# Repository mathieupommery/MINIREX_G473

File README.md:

# STM32G473 Flight Controller (20x20mm)

# NEWS : 
* V2 reduced cost by changing part of the compoment to asian brand, assembly now possible with jlc and lcsc part stock, a price per unit produced graph is disponible below 

## Overview
High-performance flight controller based on the **STM32G473** MCU, featuring a compact 20x20mm mounting pattern. This board is specifically designed for high-voltage builds (up to 12S) and high-speed processing, utilizing a 6-layer PCB stackup with all components mounted on a single side for optimal integration and cooling.
## Hardware Visuals

### PCB View (V1)

### CAD View (V1)

## Technical Specifications
### Core System
* **MCU:** STM32G473 (Cortex-M4, 170MHz)
* **IMU:** ICM-42688-P (Ultra-low noise 6-axis gyro)
* **Blackbox:** 16M-bit (2MB) Onboard Flash
* **PCB:** 6-layer, single-sided compoment 

### Power Management
* **Main Buck Regulator:** LMR51625
    * **Input Voltage:** 7V to 55V
    * **Output:** 5V @ 2.5A Max
* **Dual LDO Regulation:** Two independent LDL212PV33R (1.2A each)
    * **LDO 1:** Dedicated to MCU and Flash memory
    * **LDO 2:** Dedicated to the ICM-42688-P sensor for maximum signal purity

### Protection & Hardware Robustness
* **USB Protection:** Integrated **TVS Diodes** (Transient Voltage Suppressors) on the USB port to protect the MCU against electrostatic discharge (ESD) and short-circuits caused by humidity or debris.
* **Filtering:** High-quality ceramic capacitors and dedicated power planes for a low noise floor.

### Connectivity & Interface
* **Connectors:** 2x JST-SH 1.0mm ports (DJI/Digital VTX and ESC)
* **Status LEDs:** 4x Onboard diagnostic LEDs:
    * 2x Betaflight Status (Green/Blue)
    * 1x 3.3V MCU Power
    * 1x 3.3V Sensor Power
    * many soldering pads to add GPS, buzzer, led, or IO 

## Cost (BOM)
## Bill of Materials (BOM) Cost Estimation

The following table demonstrates the estimated component costs based on Mouser volume pricing. The unit price of each component dynamically adapts to the total quantity required for the entire production batch (1, 100, or 1000 boards). 

*Prices are estimates in USD and do not include PCB manufacturing or assembly costs.*

| Component / Value | Mouser Ref. | Qty/Board | Unit Price (1 Bd) | Unit Price (100 Bds) | Unit Price (1k Bds) | Total 1 Bd | Total 100 Bds | Total 1k Bds |
| :--- | :--- | :---: | :---: | :---: | :---: | :---: | :---: | :---: |
| 100n | 710-885012104005 | 13 | $0.080 | $0.010 | $0.004 | $1.04 | $13.00 | $52.00 |
| 10n | 710-885012104014 | 1 | $0.120 | $0.030 | $0.010 | $0.12 | $3.00 | $10.00 |
| 1u | 710-885012105012 | 3 | $0.180 | $0.060 | $0.030 | $0.54 | $18.00 | $90.00 |
| 4.7u | 710-885012105012 | 3 | $0.180 | $0.060 | $0.030 | $0.54 | $18.00 | $90.00 |
| 0.1u | 81-GRM155R62A104ME4J | 1 | $0.100 | $0.020 | $0.010 | $0.10 | $2.00 | $10.00 |
| 2.2u | 710-885012105007 | 1 | $0.220 | $0.080 | $0.040 | $0.22 | $8.00 | $40.00 |
| 2.2u | 81-GRT21BD72A225KE13 | 2 | $0.240 | $0.090 | $0.050 | $0.48 | $18.00 | $100.00 |
| 47u | 81-GRM21BR61A476ME5K | 2 | $0.550 | $0.220 | $0.120 | $1.10 | $44.00 | $240.00 |
| USB4110-GF-A | 710-629722000214 | 1 | $1.150 | $0.850 | $0.650 | $1.15 | $85.00 | $650.00 |
| LED 150040BS73240 (Blue) | 710-150040BS73240 | 1 | $0.260 | $0.120 | $0.080 | $0.26 | $12.00 | $80.00 |
| LED 150040GS73240 (Green) | 710-150040GS73240 | 1 | $0.260 | $0.120 | $0.080 | $0.26 | $12.00 | $80.00 |
| LED 150040RS73240 (Red) | 710-150040RS73240 | 2 | $0.260 | $0.120 | $0.080 | $0.52 | $24.00 | $160.00 |
| STM32G473CEU6 | 511-STM32G473CEU6 | 1 | $7.580 | $5.450 | $4.800 | $7.58 | $545.00 | $4800.00 |
| 5.1k | 667-ERJ-1GNF5101C | 2 | $0.100 | $0.010 | $0.005 | $0.20 | $2.00 | $10.00 |
| 100k | 667-ERJ-1GNF1003C | 2 | $0.100 | $0.010 | $0.005 | $0.20 | $2.00 | $10.00 |
| 10k | 667-ERJ-1GNF1002C | 3 | $0.100 | $0.010 | $0.005 | $0.30 | $3.00 | $15.00 |
| 1k | 667-ERJ-1GNF1001C | 6 | $0.100 | $0.010 | $0.005 | $0.60 | $6.00 | $30.00 |
| 20k | 667-ERJ-1GNF2002C | 1 | $0.100 | $0.010 | $0.005 | $0.10 | $1.00 | $5.00 |
| 19.1k | 667-ERJ-1GNF1912C | 1 | $0.100 | $0.010 | $0.005 | $0.10 | $1.00 | $5.00 |
| 22R | 667-ERJ-1GNF22R0C | 7 | $0.100 | $0.010 | $0.005 | $0.70 | $7.00 | $35.00 |
| 100R | 667-ERJ-1GNF1000C | 1 | $0.100 | $0.010 | $0.005 | $0.10 | $1.00 | $5.00 |
| Ferrite 74279220800 | 710-74279220800 | 1 | $0.140 | $0.040 | $0.020 | $0.14 | $4.00 | $20.00 |
| Inductor 74479335329247 | 710-74479335329247 | 1 | $0.780 | $0.450 | $0.320 | $0.78 | $45.00 | $320.00 |
| JST SH 6-pin | 306-M06BSRSSTBLFSNPP | 1 | $0.640 | $0.420 | $0.310 | $0.64 | $42.00 | $310.00 |
| LDO LDL212PV33R | 511-LDL212PV33R | 2 | $0.530 | $0.380 | $0.280 | $1.06 | $76.00 | $560.00 |
| Flash MX25R1635FZUIH0 | 95-25R1635FZUIH0TR | 1 | $1.840 | $1.150 | $0.950 | $1.84 | $115.00 | $950.00 |
| TVS SP3222-02ETG | 576-SP3222-02ETG | 1 | $0.420 | $0.220 | $0.150 | $0.42 | $22.00 | $150.00 |
| Switch 435151014824 | 710-435151014824 | 1 | $0.850 | $0.520 | $0.380 | $0.85 | $52.00 | $380.00 |
| MOSFET 2N7002KQBZ | 771-2N7002KQBZ | 1 | $0.180 | $0.060 | $0.030 | $0.18 | $6.00 | $30.00 |
| Osc CSTNE8M00GH5C000R0 | 81-CSTNE8M00GH5C000R | 1 | $0.450 | $0.240 | $0.160 | $0.45 | $24.00 | $160.00 |
| IMU ICM-42688-P | 410-ICM-42688-P | 1 | $4.860 | $3.550 | $2.900 | $4.86 | $355.00 | $2900.00 |
| JST SH 8-pin | 306-SM08BSRSSTB | 1 | $0.720 | $0.480 | $0.350 | $0.72 | $48.00 | $350.00 |
| Diode BAT60JFILM | 511-BAT60JFILM | 2 | $0.280 | $0.110 | $0.060 | $0.56 | $22.00 | $120.00 |
| Buck LMR51625YFDDCR | 595-LMR51625YFDDCR | 1 | $1.250 | $0.880 | $0.650 | $1.25 | $88.00 | $650.00 |
| **TOTAL COST (BOM)** | **-** | **-** | **-** | **-** | **-** | **$29.96** | **$1724.00** | **$13417.00** |
| **AVERAGE PRICE PER BOARD** | **-** | **-** | **-** | **-** | **-** | **$29.96** | **$17.24** | **$13.42** |

## Cost (BOM) V2
V2 version is here for cost optimisation purposes and for the possibility to assemble it completly on jlcpcb with lcsc compoment part, i changed few compoment like Nmos for buzzer or boot button, and i priviledged asian brand here is a graph with the cost per unit according to unit produced : 

## Hardware Design Principles
The 6-layer design ensures superior EMI shielding and thermal dissipation. 
stackup: signal-gnd-signal-gnd-power-gnd   
provide shielded power from signal and from the outside.

## Result and test : 

### Before reflow : 

###  Mounted on apex evo 5 inch : 

###  Test in fly :

> La vidéo de démonstration est disponible ici : [DOC/image_v1/video.mp4](./DOC/v1_image/vid.mp4)

## License
Creative Commons Attribution-NonCommercial-ShareAlike 4.0 International.

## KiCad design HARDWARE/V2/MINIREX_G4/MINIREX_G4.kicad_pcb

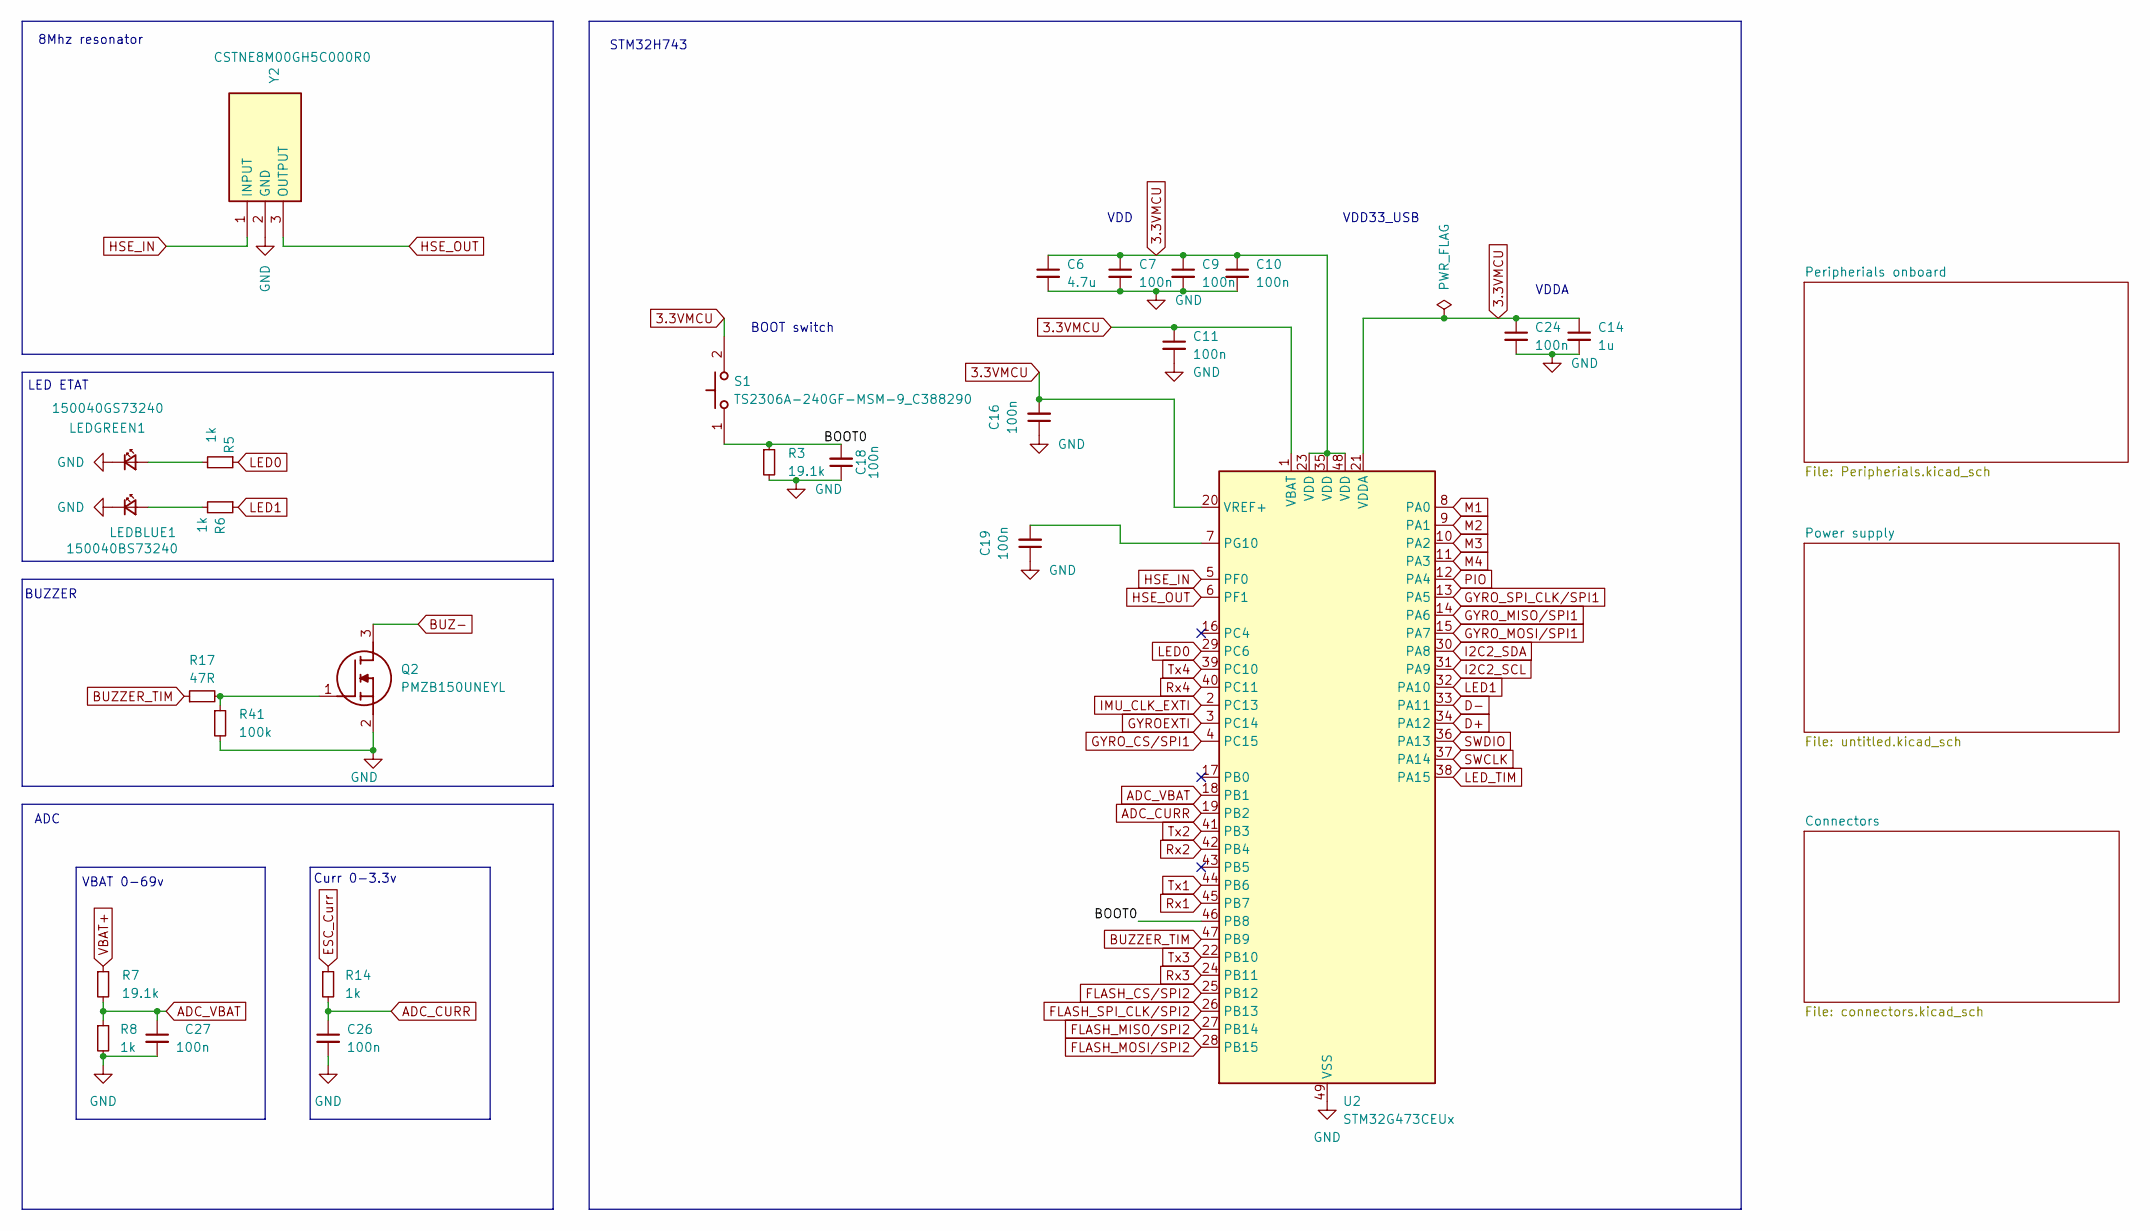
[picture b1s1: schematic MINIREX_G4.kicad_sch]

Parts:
C6: 4.7u; C_0402_1005Metric; Manufacturer_Part_Number CC0402MRX5R7BB475; Mouser Part Number 710-885012105012
C7, C9, C10, C11, C16, C18, C19, C24, C26, C27: 100n; C_0201_0603Metric_Pad0.64x0.40mm_HandSolder; Manufacturer_Part_Number CC0201KRX5R8BB104; Mouser Part Number 710-885012104005
C14: 1u; C_0402_1005Metric; Manufacturer_Part_Number CC0402KRX5R7BB105; Mouser Part Number 710-885012105012
LEDBLUE1: 150040BS73240; LED_0402_1005Metric; Manufacturer_Part_Number XL-1005UBC; Mouser Part Number 710-150040BS73240
LEDGREEN1: 150040GS73240; LED_0402_1005Metric; Manufacturer_Part_Number SZYY0402G; Mouser Part Number 710-150040GS73240
Q2: PMZB150UNEYL; Manufacturer_Part_Number TPM2025NP3; Mouser Part Number 771-PMZB150UNEYL
R3, R7: 19.1k; R_0201_0603Metric_Pad0.64x0.40mm_HandSolder; Manufacturer_Part_Number RC0201FR-0719K6L; Mouser Part Number 667-ERJ-1GNF1002C
R5, R6, R8, R14: 1k; R_0201_0603Metric_Pad0.64x0.40mm_HandSolder; Manufacturer_Part_Number RC0201FR-071KL; Mouser Part Number 667-ERJ-1GNF1001C
R17: 47R; R_0201_0603Metric_Pad0.64x0.40mm_HandSolder; Manufacturer_Part_Number RC0201FR-0747RL; Mouser Part Number 667-ERJ-1GNF22R0C
R41: 100k; R_0201_0603Metric_Pad0.64x0.40mm_HandSolder; Manufacturer_Part_Number RC0201FR-07100KL; Mouser Part Number 667-ERJ-1GNF1003C
S1: TS2306A-240GF-MSM-9_C388290; TS2306A240GFMSM9_C388290; Manufacturer_Part_Number TS2306A-240GF-MSM-9_C388290; LCSC Part Number C2976675
U2: STM32G473CEUx; QFN-48-1EP_7x7mm_P0.5mm_EP5.6x5.6mm; Manufacturer_Part_Number STM32G473CEU6; Mouser Part Number 511-STM32G473CEU6
Y2: CSTNE8M00GH5C000R0; CSTNE12M0GH5L000R0; Mouser Part Number 81-CSTNE8M00GH5C000R

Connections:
3.3VMCU: C6.1, C7.1, C9.1, C10.1, C11.1, C14.1, C16.2, C24.1, S1.2 (COM), U2.1 (VBAT), U2.20 (VREF+), U2.21 (VDDA), U2.23 (VDD), U2.35 (VDD), U2.48 (VDD); also elsewhere on the board
/BOOT0: C18.2, R3.1, S1.1 (NO), U2.46 (PB8)
ADC_CURR: C26.1, R14.2, U2.19 (PB2)
ADC_VBAT: C27.1, R7.2, R8.1, U2.18 (PB1)
BUZ-: Q2.3 (D); also elsewhere on the board
BUZZER_TIM: R17.1, U2.47 (PB9)
D+: U2.34 (PA12); also elsewhere on the board
D-: U2.33 (PA11); also elsewhere on the board
ESC_Curr: R14.1; also elsewhere on the board
FLASH_CS/SPI2: U2.25 (PB12); also elsewhere on the board
FLASH_MISO/SPI2: U2.27 (PB14); also elsewhere on the board
FLASH_MOSI/SPI2: U2.28 (PB15); also elsewhere on the board
FLASH_SPI_CLK/SPI2: U2.26 (PB13); also elsewhere on the board
GND: C6.2, C7.2, C9.2, C10.2, C11.2, C14.2, C16.1, C18.1, C19.1, C24.2, C26.2, C27.2, LEDBLUE1.1 (K), LEDGREEN1.1 (K), Q2.2 (S), R3.2, R8.2, R41.2, U2.49 (VSS), Y2.2 (GND); also elsewhere on the board
GYROEXTI: U2.3 (PC14); also elsewhere on the board
GYRO_CS/SPI1: U2.4 (PC15); also elsewhere on the board
GYRO_MISO/SPI1: U2.14 (PA6); also elsewhere on the board
GYRO_MOSI/SPI1: U2.15 (PA7); also elsewhere on the board
GYRO_SPI_CLK/SPI1: U2.13 (PA5); also elsewhere on the board
HSE_IN: U2.5 (PF0), Y2.1 (INPUT)
HSE_OUT: U2.6 (PF1), Y2.3 (OUTPUT)
I2C2_SCL: U2.31 (PA9); also elsewhere on the board
I2C2_SDA: U2.30 (PA8); also elsewhere on the board
IMU_CLK_EXTI: U2.2 (PC13); also elsewhere on the board
LED0: R5.1, U2.29 (PC6)
LED1: R6.1, U2.32 (PA10)
LED_TIM: U2.38 (PA15); also elsewhere on the board
M1: U2.8 (PA0); also elsewhere on the board
M2: U2.9 (PA1); also elsewhere on the board
M3: U2.10 (PA2); also elsewhere on the board
M4: U2.11 (PA3); also elsewhere on the board
unnamed: LEDBLUE1.2 (A), R6.2
unnamed: LEDGREEN1.2 (A), R5.2
unnamed: Q2.1 (G), R17.2, R41.1
unnamed: C19.2, U2.7 (PG10)
PIO: U2.12 (PA4); also elsewhere on the board
Rx1: U2.45 (PB7); also elsewhere on the board
Rx2: U2.42 (PB4); also elsewhere on the board
Rx3: U2.24 (PB11); also elsewhere on the board
Rx4: U2.40 (PC11); also elsewhere on the board
SWCLK: U2.37 (PA14); also elsewhere on the board
SWDIO: U2.36 (PA13); also elsewhere on the board
Tx1: U2.44 (PB6); also elsewhere on the board
Tx2: U2.41 (PB3); also elsewhere on the board
Tx3: U2.22 (PB10); also elsewhere on the board
Tx4: U2.39 (PC10); also elsewhere on the board
VBAT+: R7.1; also elsewhere on the board

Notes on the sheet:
VDD33_USB
VDDA
BUZZER
STM32H743
ADC
Curr 0-3.3v
LED ETAT
BOOT switch
VDD
8Mhz resonator
VBAT 0-69v

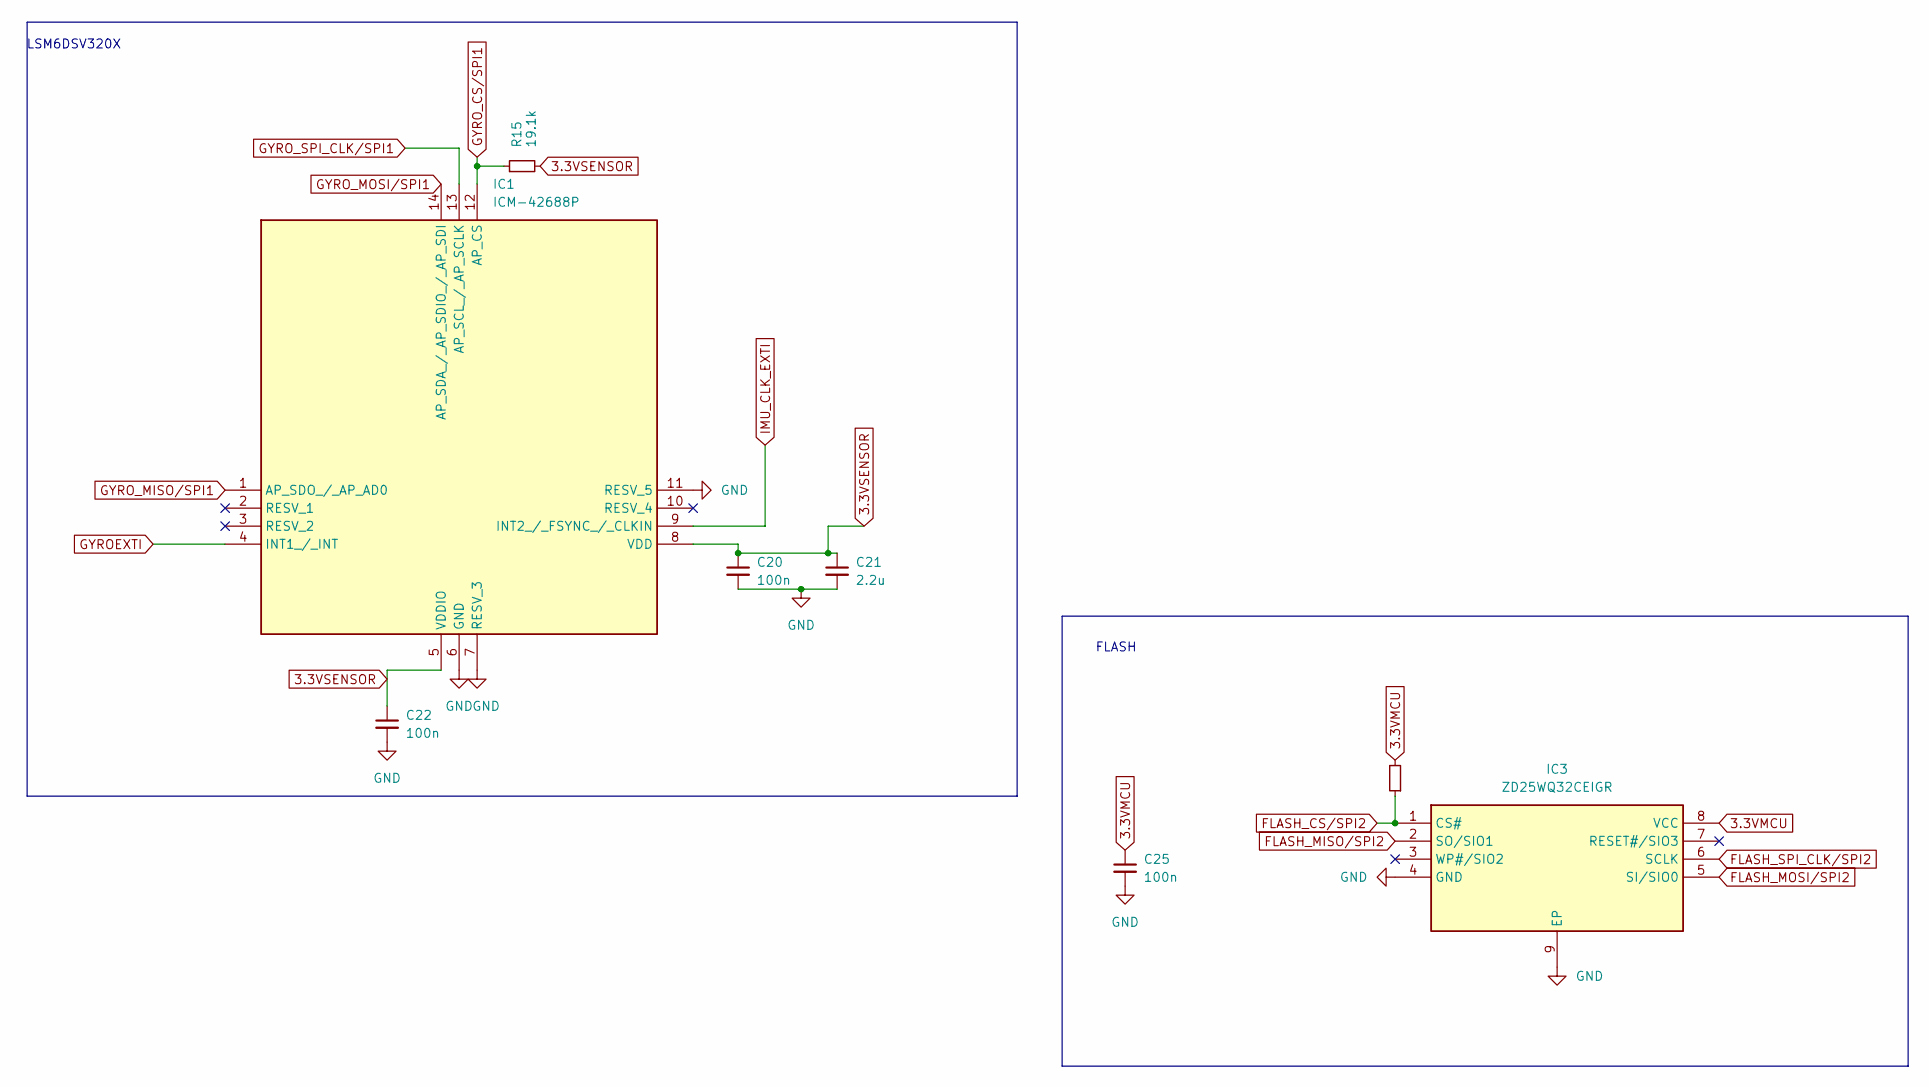
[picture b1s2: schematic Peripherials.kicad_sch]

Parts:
C20, C25: 100n; C_0201_0603Metric_Pad0.64x0.40mm_HandSolder; Manufacturer_Part_Number CC0201KRX5R8BB104; Mouser Part Number 710-885012104005
C21: 2.2u; C_0402_1005Metric; Manufacturer_Part_Number CC0402KRX5R7BB225; Mouser Part Number 710-885012105007
C22: 100n; C_0201_0603Metric_Pad0.64x0.40mm_HandSolder; Manufacturer_Part_Number CC0201KRX5R8BB104; Mouser Part Number 710-885012104014
IC1: ICM-42688P; IIM42352; Mouser Part Number 410-ICM-42688-P
IC3: ZD25WQ32CEIGR; SON50P300X200X60-9N; Manufacturer_Part_Number ZD25WQ32CEIGR; Mouser Part Number 95-25R1635FZUIH0TR
R9, R15: 19.1k; R_0201_0603Metric_Pad0.64x0.40mm_HandSolder; Manufacturer_Part_Number RC0201FR-0719K6L; Mouser Part Number 667-ERJ-1GNF1002C

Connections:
3.3VMCU: C25.1, IC3.8 (VCC), R9.2; also elsewhere on the board
3.3VSENSOR: C20.1, C21.1, C22.1, IC1.5 (VDDIO), IC1.8 (VDD), R15.2; also elsewhere on the board
FLASH_CS/SPI2: IC3.1 (CS#), R9.1; also elsewhere on the board
FLASH_MISO/SPI2: IC3.2 (SO/SIO1); also elsewhere on the board
FLASH_MOSI/SPI2: IC3.5 (SI/SIO0); also elsewhere on the board
FLASH_SPI_CLK/SPI2: IC3.6 (SCLK); also elsewhere on the board
GND: C20.2, C21.2, C22.2, C25.2, IC1.6 (GND), IC1.7 (RESV_3), IC1.11 (RESV_5), IC3.4 (GND), IC3.9 (EP); also elsewhere on the board
GYROEXTI: IC1.4 (INT1_/_INT); also elsewhere on the board
GYRO_CS/SPI1: IC1.12 (AP_CS), R15.1; also elsewhere on the board
GYRO_MISO/SPI1: IC1.1 (AP_SDO_/_AP_AD0); also elsewhere on the board
GYRO_MOSI/SPI1: IC1.14 (AP_SDA_/_AP_SDIO_/_AP_SDI); also elsewhere on the board
GYRO_SPI_CLK/SPI1: IC1.13 (AP_SCL_/_AP_SCLK); also elsewhere on the board
IMU_CLK_EXTI: IC1.9 (INT2_/_FSYNC_/_CLKIN); also elsewhere on the board

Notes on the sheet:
FLASH
LSM6DSV320X

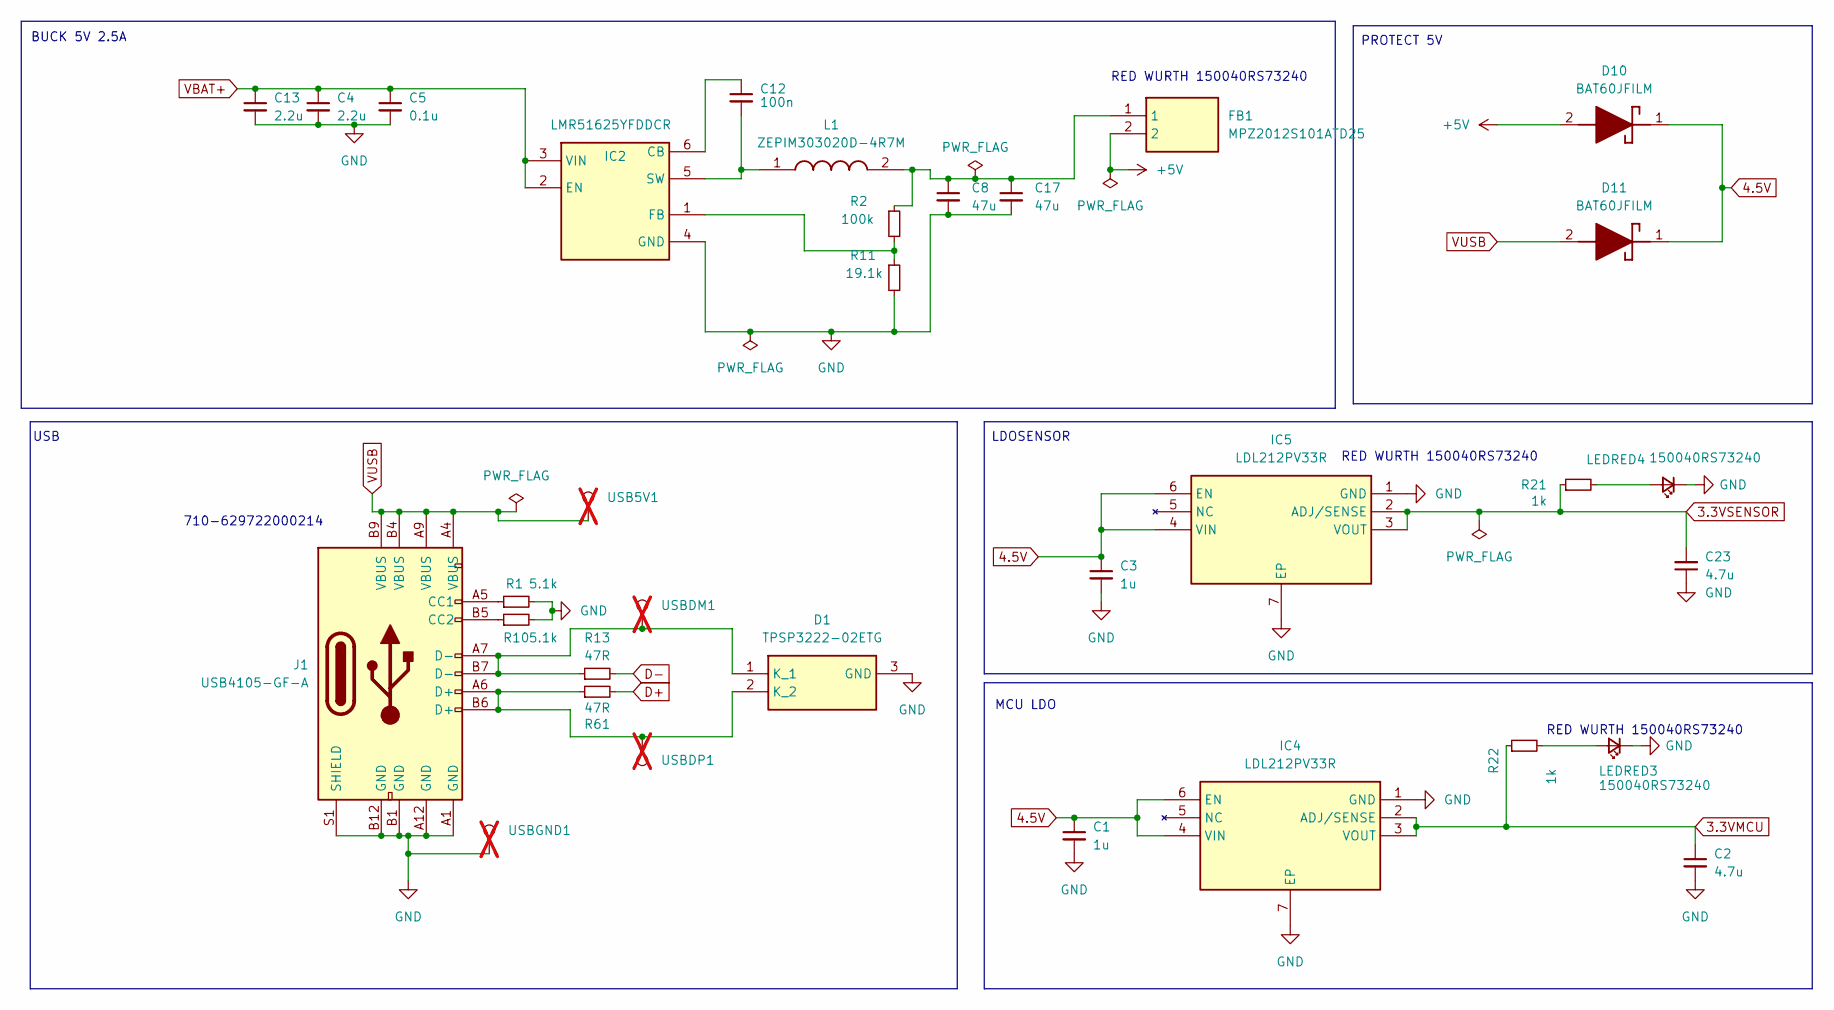
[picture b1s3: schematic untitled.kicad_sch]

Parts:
C1, C3: 1u; C_0402_1005Metric; Manufacturer_Part_Number CC0402KRX5R7BB105; Mouser Part Number 710-885012105012
C2, C23: 4.7u; C_0402_1005Metric; Manufacturer_Part_Number CC0402MRX5R7BB475; Mouser Part Number 710-885012105012
C4, C13: 2.2u; C_0805_2012Metric; Manufacturer_Part_Number GRM21BD72A225KE01L; Mouser Part Number 81-GRT21BD72A225KE13
C5: 0.1u; C_0402_1005Metric; Manufacturer_Part_Number GRM155R62A104KE14D; Mouser Part Number 81-GRM155R62A104ME4J
C8, C17: 47u; C_0805_2012Metric; Manufacturer_Part_Number GRM21BR61A476ME15K; Mouser Part Number 81-GRM21BR61A476ME5K
C12: 100n; C_0201_0603Metric_Pad0.64x0.40mm_HandSolder; Manufacturer_Part_Number CC0201KRX5R8BB104; Mouser Part Number 710-885012104005
D1: TPSP3222-02ETG; SP322202ETG; Manufacturer_Part_Number TPSP3222-02ETG; Mouser Part Number 576-SP3222-02ETG
D10, D11: BAT60JFILM; SOD2513X117N; Mouser Part Number 511-BAT60JFILM
FB1: MPZ2012S101ATD25; BEADC2012X90N; Manufacturer_Part_Number MPZ2012S101ATD25; Mouser Part Number 710-74279220800
IC2: LMR51625YFDDCR; SOT95P280X110-6N; Manufacturer_Part_Number LMR51625YFDDCR; Mouser Part Number 595-LMR51625YFDDCR
IC4, IC5: LDL212PV33R; SON50P200X200X80-7N-D; Manufacturer_Part_Number LDL212PV33R; Mouser Part Number 511-LDL212PV33R
J1: USB4105-GF-A; USB_C_Receptacle_GCT_USB4105-xx-A_16P_TopMnt_Horizontal; Manufacturer_Part_Number USB4105-GF-A; Mouser Part Number 710-629722000214
L1: ZEPIM303020D-4R7M; INDC3532X200N; Manufacturer_Part_Number ZEPIM303020D-4R7M; Mouser Part Number 710-74479335329247
LEDRED3, LEDRED4: 150040RS73240; LED_0402_1005Metric; Manufacturer_Part_Number TZ-P2-0402RTIA1-0.45T; Mouser Part Number 710-150040RS73240
R1, R10: 5.1k; R_0201_0603Metric_Pad0.64x0.40mm_HandSolder; Manufacturer_Part_Number RC0201FR-075K1L; Mouser Part Number 667-ERJ-1GNF5101C
R2: 100k; R_0201_0603Metric_Pad0.64x0.40mm_HandSolder; Manufacturer_Part_Number RC0201FR-07100KL; Mouser Part Number 667-ERJ-1GNF1003C
R11: 19.1k; R_0201_0603Metric_Pad0.64x0.40mm_HandSolder; Manufacturer_Part_Number RC0201FR-0719K6L; Mouser Part Number 667-ERJ-1GNF1002C
R13, R61: 47R; R_0201_0603Metric_Pad0.64x0.40mm_HandSolder; Manufacturer_Part_Number RC0201FR-0747RL; Mouser Part Number 667-ERJ-1GNF22R0C
R21, R22: 1k; R_0201_0603Metric_Pad0.64x0.40mm_HandSolder; Manufacturer_Part_Number RC0201FR-071KL; Mouser Part Number 667-ERJ-1GNF1001C
USB5V1: TestPoint; PAD_1.5mmx1.5mm; not fitted
USBDM1: TestPoint; PAD_1.5mmx1.5mm; not fitted
USBDP1: TestPoint; PAD_1.5mmx1.5mm; not fitted
USBGND1: TestPoint; PAD_1.5mmx1.5mm; not fitted

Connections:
3.3VMCU: C2.1, IC4.2 (ADJ/SENSE), IC4.3 (VOUT), R22.1; also elsewhere on the board
3.3VSENSOR: C23.2, IC5.2 (ADJ/SENSE), IC5.3 (VOUT), R21.1; also elsewhere on the board
4.5V: C1.1, C3.1, D10.1 (K), D11.1 (K), IC4.4 (VIN), IC4.6 (EN), IC5.4 (VIN), IC5.6 (EN); also elsewhere on the board
+5V: D10.2 (A), FB1.2; also elsewhere on the board
D+: R61.2; also elsewhere on the board
D-: R13.2; also elsewhere on the board
GND: C1.2, C2.2, C3.2, C4.2, C5.2, C8.2, C13.2, C17.2, C23.1, D1.3 (GND), IC2.4 (GND), IC4.1 (GND), IC4.7 (EP), IC5.1 (GND), IC5.7 (EP), J1.A1 (GND), J1.A12 (GND), J1.B1 (GND), J1.B12 (GND), J1.S1 (SHIELD), LEDRED3.1 (K), LEDRED4.1 (K), R1.2, R10.2, R11.2, USBGND1.1; also elsewhere on the board
unnamed: C8.1, C17.1, FB1.1, L1.2, R2.1
unnamed: D1.1 (K_1), J1.A7 (D-), J1.B7 (D-), R13.1, USBDM1.1
unnamed: D1.2 (K_2), J1.A6 (D+), J1.B6 (D+), R61.1, USBDP1.1
unnamed: C12.1, IC2.6 (CB)
unnamed: IC2.1 (FB), R2.2, R11.1
unnamed: C12.2, IC2.5 (SW), L1.1
unnamed: J1.A5 (CC1), R1.1
unnamed: J1.B5 (CC2), R10.1
unnamed: LEDRED3.2 (A), R22.2
unnamed: LEDRED4.2 (A), R21.2
VBAT+: C4.1, C5.1, C13.1, IC2.2 (EN), IC2.3 (VIN); also elsewhere on the board
VUSB: D11.2 (A), J1.A4 (VBUS), J1.A9 (VBUS), J1.B4 (VBUS), J1.B9 (VBUS), USB5V1.1

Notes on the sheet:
LDOSENSOR
PROTECT 5V
RED WURTH 150040RS73240
BUCK 5V 2.5A
MCU LDO
USB
710-629722000214

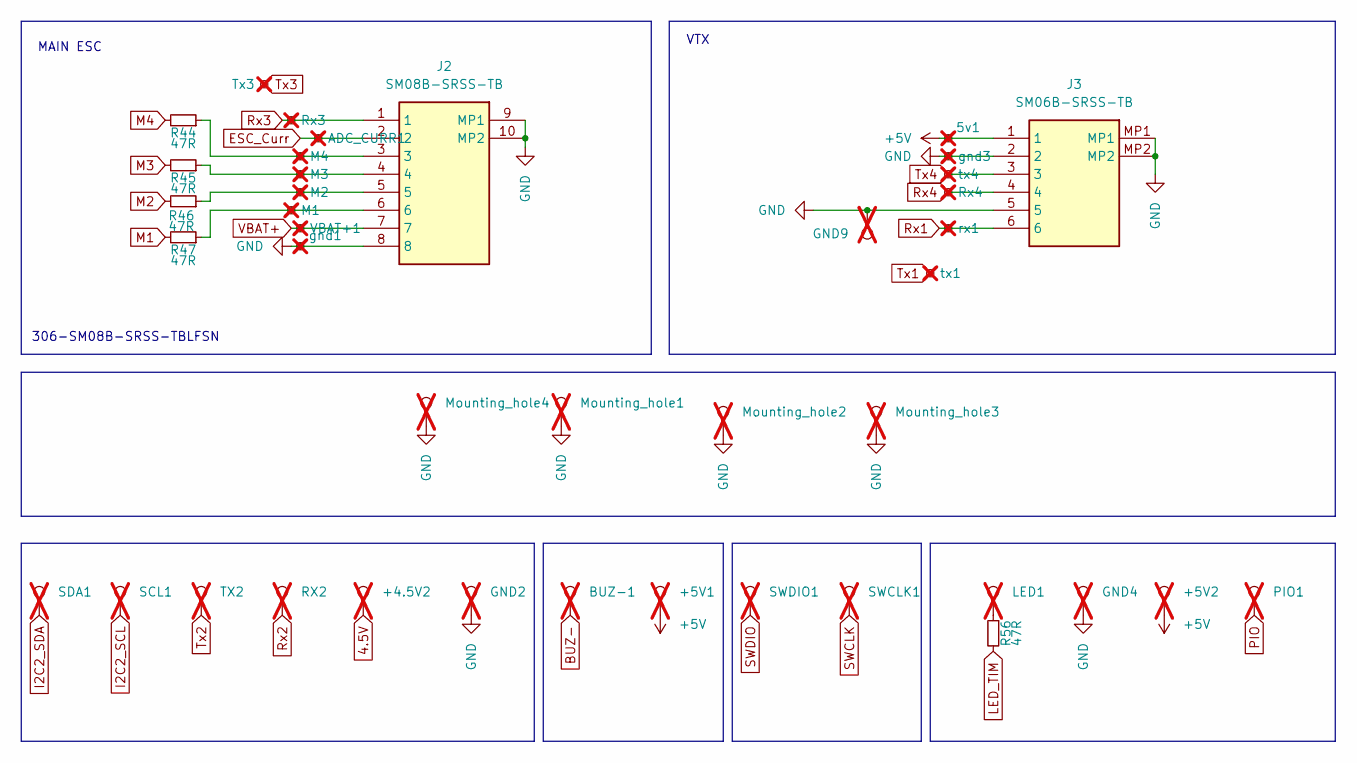
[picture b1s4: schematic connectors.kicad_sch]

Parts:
5v1: TestPoint_Small; PAD_1.5mmx1.5mm_hole; not fitted
+4.5V2, +5V1, +5V2: TestPoint; PAD_1.5mmx1.5mm; not fitted
ADC_CURR1: TestPoint_Small; PAD_1.5mmx1.5mm_hole; not fitted
BUZ-1: TestPoint; PAD_1.5mmx1.5mm; not fitted
GND2, GND4: TestPoint; PAD_1.5mmx1.5mm; not fitted
GND9: TestPoint; PAD_1.5mmx1.5mm_hole; not fitted
J2: SM08B-SRSS-TB; SM08BSRSSTB; Manufacturer_Part_Number SM08B-SRSS-TB; Mouser Part Number 306-SM08BSRSSTB
J3: SM06B-SRSS-TB; SM06BSRSSTB; Manufacturer_Part_Number SM06B-SRSS-TB; Mouser Part Number 306-M06BSRSSTBLFSNPP
LED1: TestPoint; PAD_1.5mmx1.5mm; not fitted
M1, M2, M3, M4: TestPoint_Small; PAD_1.5mmx1.5mm_hole; not fitted
Mounting_hole1, Mounting_hole2, Mounting_hole3, Mounting_hole4: TestPoint; MountingHole_3.2mm_M3_Pad_Via; not fitted
PIO1: TestPoint; PAD_1.5mmx1.5mm; not fitted
R44, R45, R46, R47, R56: 47R; R_0201_0603Metric_Pad0.64x0.40mm_HandSolder; Manufacturer_Part_Number RC0201FR-0747RL; Mouser Part Number 667-ERJ-1GNF22R0C
RX2: TestPoint; PAD_1.5mmx1.5mm; not fitted
Rx3, Rx4: TestPoint_Small; PAD_1.5mmx1.5mm_hole; not fitted
SCL1: TestPoint; PAD_1.5mmx1.5mm; not fitted
SDA1: TestPoint; PAD_1.5mmx1.5mm; not fitted
SWCLK1: TestPoint; 1mm_circle; not fitted
SWDIO1: TestPoint; 1mm_circle; not fitted
TX2: TestPoint; PAD_1.5mmx1.5mm; not fitted
Tx3: TestPoint_Small; PAD_1.5mmx1.5mm_hole; not fitted
VBAT+1: TestPoint_Small; PAD_1.5mmx1.5mm_hole; not fitted
gnd1, gnd3: TestPoint_Small; PAD_1.5mmx1.5mm_hole; not fitted
rx1: TestPoint_Small; PAD_1.5mmx1.5mm_hole; not fitted
tx1, tx4: TestPoint_Small; PAD_1.5mmx1.5mm_hole; not fitted

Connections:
4.5V: +4.5V2.1; also elsewhere on the board
+5V: 5v1.1, +5V1.1, +5V2.1, J3.1; also elsewhere on the board
BUZ-: BUZ-1.1; also elsewhere on the board
ESC_Curr: ADC_CURR1.1, J2.2; also elsewhere on the board
GND: GND2.1, GND4.1, GND9.1, J2.8, J2.9 (MP1), J2.10 (MP2), J3.2, J3.5, J3.MP1, J3.MP2, Mounting_hole1.1, Mounting_hole2.1, Mounting_hole3.1, Mounting_hole4.1, gnd1.1, gnd3.1; also elsewhere on the board
I2C2_SCL: SCL1.1; also elsewhere on the board
I2C2_SDA: SDA1.1; also elsewhere on the board
LED_TIM: R56.2; also elsewhere on the board
M1: R47.2; also elsewhere on the board
M2: R46.2; also elsewhere on the board
M3: R45.2; also elsewhere on the board
M4: R44.2; also elsewhere on the board
unnamed: J2.3, M4.1, R44.1
unnamed: J2.4, M3.1, R45.1
unnamed: J2.5, M2.1, R46.1
unnamed: J2.6, M1.1, R47.1
unnamed: LED1.1, R56.1
PIO: PIO1.1; also elsewhere on the board
Rx1: J3.6, rx1.1; also elsewhere on the board
Rx2: RX2.1; also elsewhere on the board
Rx3: J2.1, Rx3.1; also elsewhere on the board
Rx4: J3.4, Rx4.1; also elsewhere on the board
SWCLK: SWCLK1.1; also elsewhere on the board
SWDIO: SWDIO1.1; also elsewhere on the board
Tx1: tx1.1; also elsewhere on the board
Tx2: TX2.1; also elsewhere on the board
Tx3: Tx3.1; also elsewhere on the board
Tx4: J3.3, tx4.1; also elsewhere on the board
VBAT+: J2.7, VBAT+1.1; also elsewhere on the board

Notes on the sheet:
MAIN ESC
306-SM08B-SRSS-TBLFSN
VTX

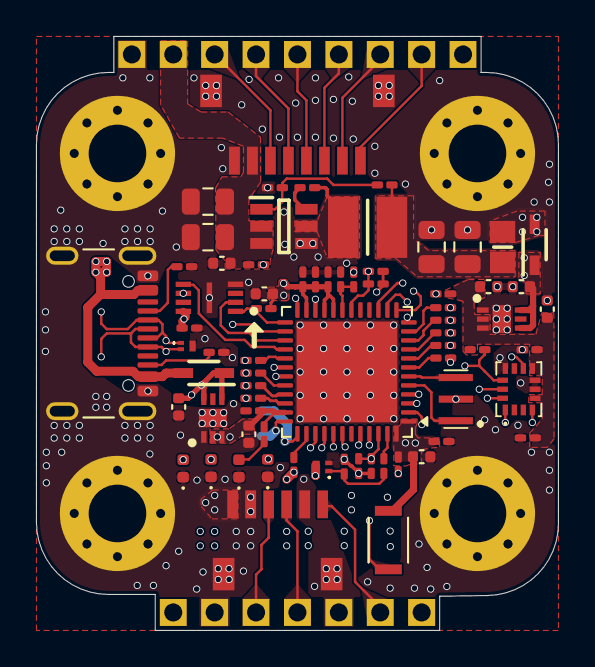
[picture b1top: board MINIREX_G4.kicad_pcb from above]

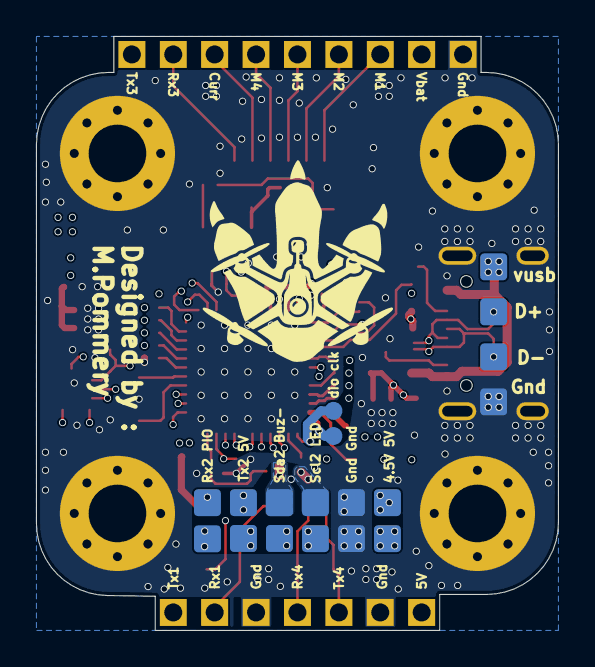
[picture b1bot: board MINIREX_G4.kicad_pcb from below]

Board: 6 copper layers, 29.0 x 33.0 mm, 108 parts (18 on the bottom side), 66 nets.

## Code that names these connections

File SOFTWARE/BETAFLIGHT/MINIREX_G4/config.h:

/*
 * This file is part of Betaflight.
 *
 * Betaflight is free software. You can redistribute this software
 * and/or modify this software under the terms of the GNU General
 * Public License as published by the Free Software Foundation,
 * either version 3 of the License, or (at your option) any later
 * version.
 *
 * Betaflight is distributed in the hope that it will be useful,
 * but WITHOUT ANY WARRANTY; without even the implied warranty of
 * MERCHANTABILITY or FITNESS FOR A PARTICULAR PURPOSE.
 *
 * See the GNU General Public License for more details.
 *
 * You should have received a copy of the GNU General Public
 * License along with this software.
 *
 * If not, see <http://www.gnu.org/licenses/>.
 */

#pragma once

#define FC_TARGET_MCU     STM32G47X

#define BOARD_NAME        MINIREX_G4
#define MANUFACTURER_ID   POMMERY

#define USE_ACC
#define USE_ACC_SPI_ICM42688P
#define USE_GYRO
#define USE_GYRO_CLKIN
#define USE_GYRO_SPI_ICM42688P
#define USE_FLASH
#define USE_FLASH_M25P16

#define BEEPER_PIN           PB9

#define MOTOR1_PIN           PA0
#define MOTOR2_PIN           PA1
#define MOTOR3_PIN           PA2
#define MOTOR4_PIN           PA3


#define LED_STRIP_PIN        PA15

#define UART1_TX_PIN         PB6
#define UART2_TX_PIN         PB3
#define UART3_TX_PIN         PB10
#define UART4_TX_PIN         PC10

#define UART1_RX_PIN         PB7
#define UART2_RX_PIN         PB4
#define UART3_RX_PIN         PB11
#define UART4_RX_PIN         PC11

#define I2C2_SCL_PIN         PA9
#define I2C2_SDA_PIN         PA8

#define LED0_PIN             PC6
#define LED1_PIN             PA10



#define SPI1_SCK_PIN         PA5
#define SPI1_SDI_PIN         PA6
#define SPI1_SDO_PIN         PA7
#define GYRO_1_CS_PIN        PC15
#define GYRO_1_EXTI_PIN      PC14
#define GYRO1_CLKIN_PIN      PC13
#define GYRO_1_SPI_INSTANCE  SPI1


#define SPI2_SCK_PIN         PB13
#define SPI2_SDI_PIN         PB14
#define SPI2_SDO_PIN         PB15
#define FLASH_CS_PIN         PB12
#define FLASH_SPI_INSTANCE   SPI2


#define ADC_VBAT_PIN         PB1
#define ADC_CURR_PIN         PB2


#define PINIO1_PIN           PA4

#define TIMER_PIN_MAPPING \
    TIMER_PIN_MAP( 1, MOTOR1_PIN , 2,  0) \
    TIMER_PIN_MAP( 2, MOTOR2_PIN , 2,  1) \
    TIMER_PIN_MAP( 3, MOTOR3_PIN , 2,  2) \
    TIMER_PIN_MAP( 4, MOTOR4_PIN , 2,  3) \
    TIMER_PIN_MAP( 5, LED_STRIP_PIN , 1,  4) \
    TIMER_PIN_MAP( 6, GYRO1_CLKIN_PIN , 1, -1) 

#define TIMUP2_DMA_OPT      0
#define ADC1_DMA_OPT        8
#define ADC2_DMA_OPT        7

#define DEFAULT_RX_FEATURE FEATURE_RX_SERIAL
#define SERIALRX_UART      SERIAL_PORT_USART1

#define DEFAULT_BLACKBOX_DEVICE      BLACKBOX_DEVICE_FLASH


#define DEFAULT_CURRENT_METER_SOURCE CURRENT_METER_ADC
#define DEFAULT_VOLTAGE_METER_SOURCE VOLTAGE_METER_ADC
#define DEFAULT_VOLTAGE_METER_SCALE  210
#define BEEPER_PWM_HZ 2500

#define PINIO1_BOX 40
#define GYRO_1_ALIGN                 CW0_DEG

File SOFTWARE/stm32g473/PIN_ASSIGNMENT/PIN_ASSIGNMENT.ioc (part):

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Mcu.Name=STM32G473C(B-C-E)Ux
Mcu.Package=UFQFPN48
Mcu.UserName=STM32G473CEUx
PA0.Signal=S_TIM2_CH1
PA1.Signal=S_TIM2_CH2
PA11.Mode=Device
PA11.Signal=USB_DM
PA12.Mode=Device
PA12.Signal=USB_DP
PA13.Mode=Serial_Wire
PA13.Signal=SYS_JTMS-SWDIO
PA14.Mode=Serial_Wire
PA14.Signal=SYS_JTCK-SWCLK
PA15.Signal=S_TIM8_CH1
PA2.Signal=S_TIM2_CH3
PA3.Signal=S_TIM2_CH4
PA5.Mode=Full_Duplex_Master
PA5.Signal=SPI1_SCK
PA6.Mode=Full_Duplex_Master
PA6.Signal=SPI1_MISO
PA7.Mode=Full_Duplex_Master
PA7.Signal=SPI1_MOSI
PA8.Mode=I2C
PA8.Signal=I2C2_SDA
PA9.Mode=I2C
PA9.Signal=I2C2_SCL
PB1.Signal=ADC1_IN12
PB10.Mode=Asynchronous
PB10.Signal=USART3_TX
PB11.Mode=Asynchronous
PB11.Signal=USART3_RX
PB12.Signal=SPI2_NSS
PB13.Mode=Full_Duplex_Master
PB13.Signal=SPI2_SCK
PB14.Mode=Full_Duplex_Master
PB14.Signal=SPI2_MISO
PB15.Mode=Full_Duplex_Master
PB15.Signal=SPI2_MOSI
PB2.Signal=ADC2_IN12
PB3.Mode=Asynchronous
PB3.Signal=USART2_TX
PB4.Mode=Asynchronous
PB4.Signal=USART2_RX
PB6.Mode=Asynchronous
PB6.Signal=USART1_TX
PB7.Mode=Asynchronous
PB7.Signal=USART1_RX
PB9.Signal=S_TIM8_CH3
PC10.Mode=Asynchronous
PC10.Signal=UART4_TX
PC11.Mode=Asynchronous
PC11.Signal=UART4_RX
PF0-OSC_IN.Mode=HSE-External-Oscillator
PF0-OSC_IN.Signal=RCC_OSC_IN
PF1-OSC_OUT.Mode=HSE-External-Oscillator
PF1-OSC_OUT.Signal=RCC_OSC_OUT
RCC.HSE_VALUE=8000000
RCC.SYSCLKFreq_VALUE=16000000
board=custom

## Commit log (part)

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2026-03-14 upfdate
2026-03-18 Create README.md for STM32G473 Flight Controller
    Added detailed specifications, features, and visuals for the STM32G473 flight controller.
2026-03-18 Enhance README with visuals and BOM details
    Updated hardware visuals and technical specifications, including cost breakdown and component details.
2026-03-19 picture add
2026-03-22 Add news section to README
    Added news section detailing cost reduction and assembly options.
2026-04-18 Update hardware visuals in README
    Updated hardware visuals section with images for PCB and CAD views.
2026-04-20 use gps
